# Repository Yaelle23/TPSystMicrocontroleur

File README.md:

# TPSystMicrocontroleur

# THOMAS Farima
# NOYON Yaëlle

# 1.2 Le Microcontrôleur sur Kicad
13- PB9 est relié à la masse pour inhiber l'état reset du uC.

14- Leur rôle est d'éviter la chute de tension

# 1.3 Le reste du schéma
3- C'est la première page qui indique les valeurs des condensateurs dans la datasheet

5- C'est la page 6 qui indique les condensateurs du DAC

6- La broche CS permet d'autoriser le fonctionnement

7- La broche LDAC permet d'avoir des sorties en simultanée

8- MISO n'est pas utilisé car le DAC n'envoie pas de data au uC

10- On le retrouve dans la datasheet de la sonde stlink v3

# 1.4 Affectation des empreintes
3- Ces valeurs font référence aux tailles des composants

4- LQFP, SOT-223, SOIC représentent les références des types de boitiers

#LQFP (Low Profile Quad Flat Pack ) :C'est un type de boîtier de circuit intégré destiné à être directement soudé sur circuit
imprimé.
#SOT-223 : C'est un boîtier monté en surface avec dissipateur thermique accru
#SOIC (Small Outline integrated Circuit) : Un circuit intégré à petit contour est un boîtier de circuit intégré monté en surface qui occupe une surface d'environ 30 à 50% inférieure à celle d'un boîtier double en ligne équivalent, avec une épaisseur typique inférieure de 70%.

# 3 Activation des LL drivers
2-Les fichiers générés sont liés au driver qu’on a positionné en LL :
    • main (.c et .h)
    • gpio (.c et .h)
    • adc (.c et .h)
    • spi (.c et .h)
    • stm32l0xx (.c et .h)
    • tim.c (.c et .h)
    • usart.c (.c et .h)
Ces codes nous permettent d’avoir accés à des registres différents

4-Selon la documentation de la HAL STM32L0 en plus des fonctions d’initialisation périphérique, les pilotes LL offrent un ensemble de fonctions « inline » pour un accès direct au registre. 

5-Dans le .h on définit la configuration des registres.

# 3.2 LED Simple
1-Configurer le timer de la LED pour obtenir une horloge de 16MHz et une résolution de 8bits. Ça veut dire que Counter period vaut 255.On déduis la valeur de PSC = 16000/256 = 63

# 3.2 LED avec timer
3-On veut obtenir un compteur à 1MHz ce qui signifie que la valeur de PSC doit être égal à 16. Le compteur doit reset toutes les millisecondes donc on paramètre ARR pour être égal à 1000.

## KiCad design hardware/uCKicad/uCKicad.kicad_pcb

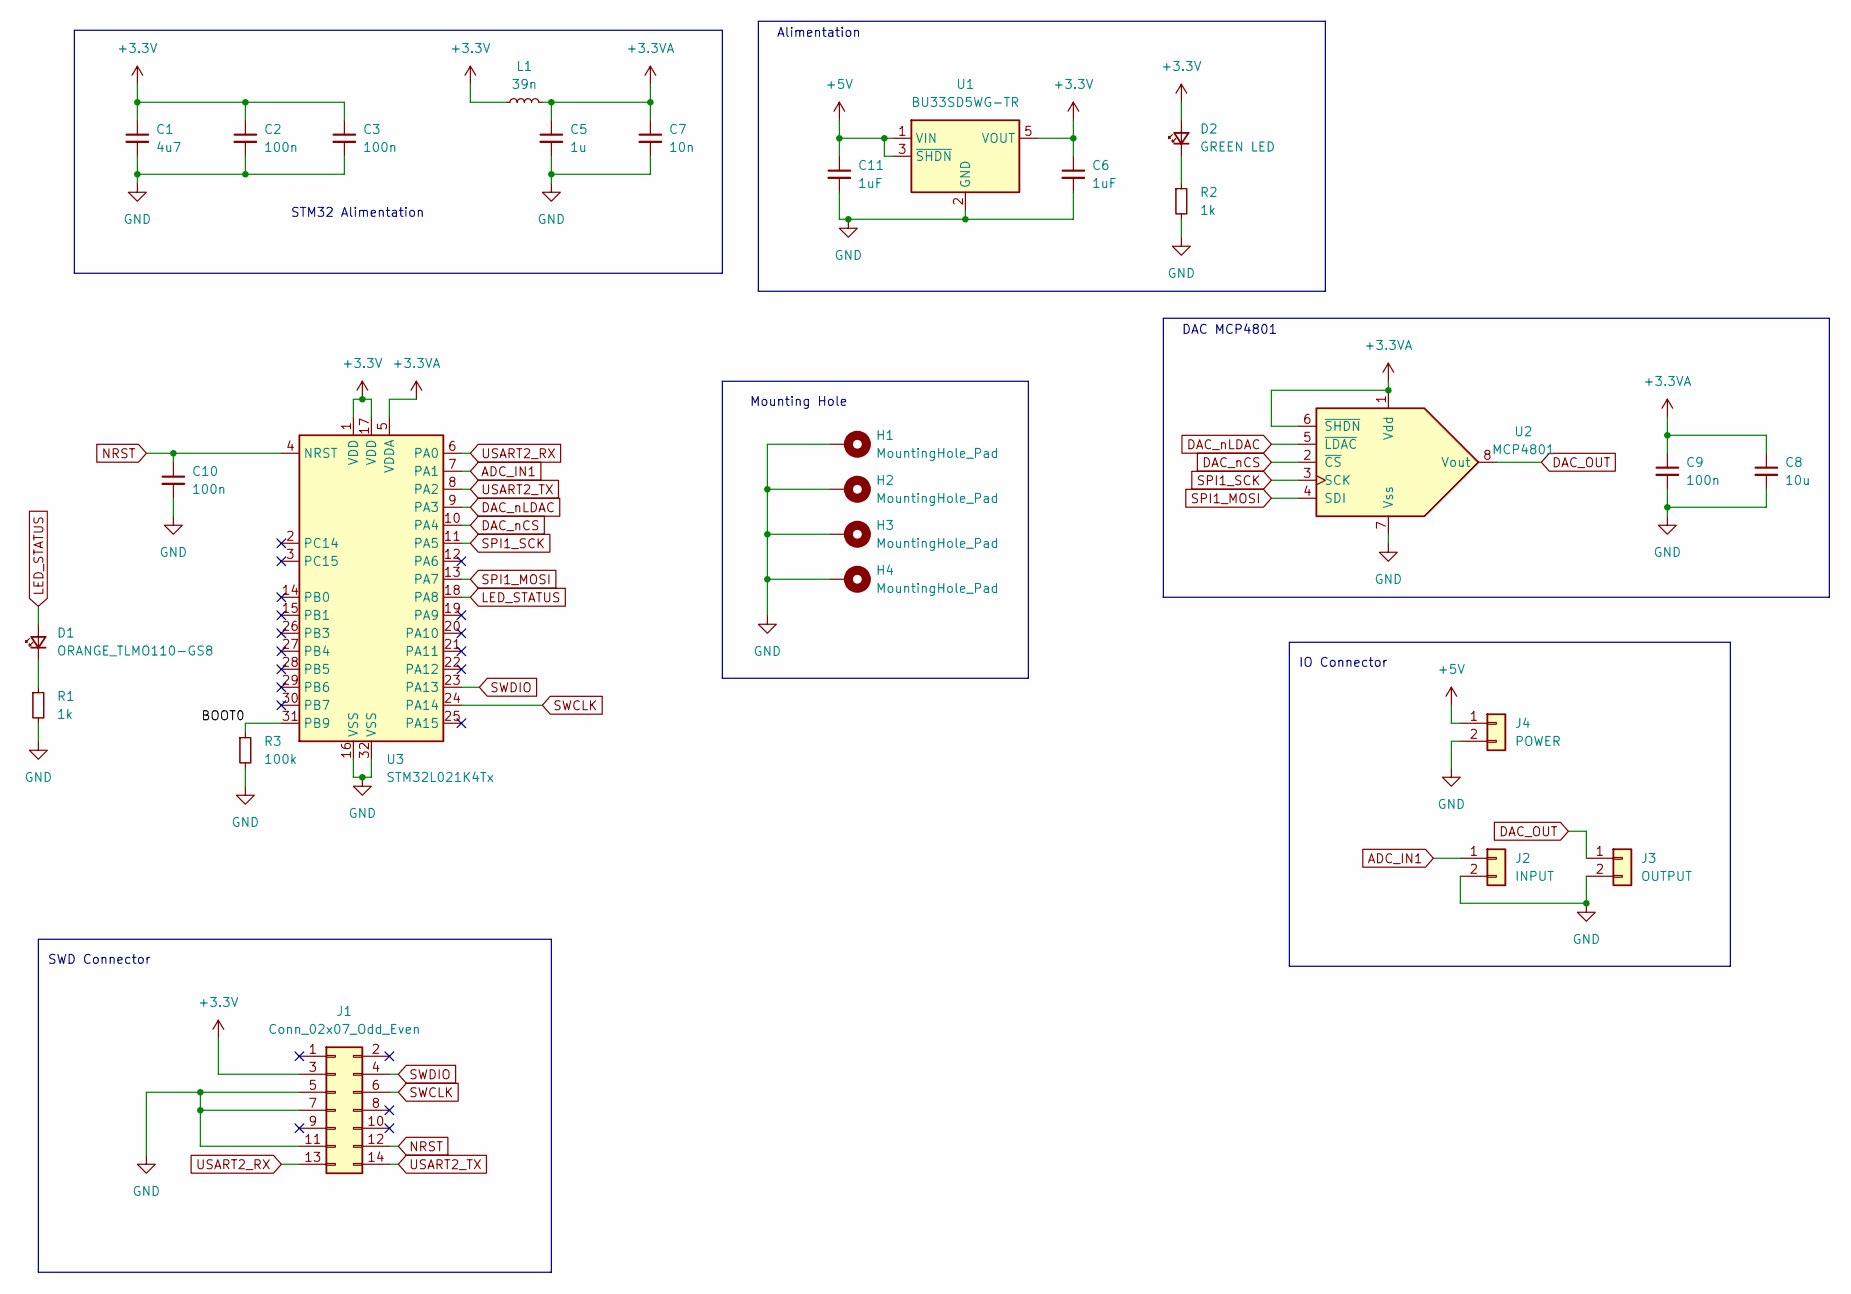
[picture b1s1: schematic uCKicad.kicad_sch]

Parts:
C1: 4u7; C_0805_2012Metric_Pad1.18x1.45mm_HandSolder
C2, C3, C9, C10: 100n; C_0805_2012Metric_Pad1.18x1.45mm_HandSolder
C5: 1u; C_0805_2012Metric_Pad1.18x1.45mm_HandSolder
C6, C11: 1uF; C_0805_2012Metric
C7: 10n; C_0805_2012Metric_Pad1.18x1.45mm_HandSolder
C8: 10u; C_0805_2012Metric
D1: ORANGE_TLMO110-GS8; LED_0603_1608Metric_Pad1.05x0.95mm_HandSolder
D2: GREEN LED; LED_0603_1608Metric_Pad1.05x0.95mm_HandSolder
H1, H2, H3, H4: MountingHole_Pad; MountingHole_3.2mm_M3_Pad
J1: Conn_02x07_Odd_Even; PinHeader_2x07_P1.27mm_Vertical_SMD
J2: INPUT; JST_XH_B2B-XH-A_1x02_P2.50mm_Vertical
J3: OUTPUT; JST_XH_B2B-XH-A_1x02_P2.50mm_Vertical
J4: POWER; JST_XH_B2B-XH-A_1x02_P2.50mm_Vertical
L1: 39n; L_0805_2012Metric_Pad1.05x1.20mm_HandSolder
R1, R2: 1k; R_0805_2012Metric_Pad1.20x1.40mm_HandSolder
R3: 100k; R_0805_2012Metric_Pad1.20x1.40mm_HandSolder
U1: BU33SD5WG-TR; SOT-23-5
U2: MCP4801; SOIC-8_3.9x4.9mm_P1.27mm
U3: STM32L021K4Tx; LQFP-32_7x7mm_P0.8mm

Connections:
+3.3V: C1.1, C2.1, C3.1, C6.1, D2.2 (A), J1.3, L1.1, U1.5 (VOUT), U3.1 (VDD), U3.17 (VDD)
+3.3VA: C5.1, C7.1, C8.1, C9.1, L1.2, U2.1 (Vdd), U2.6 (~SHDN), U3.5 (VDDA)
+5V: C11.1, J4.1, U1.1 (VIN), U1.3 (~SHDN)
/BOOT0: R3.1, U3.31 (PB9)
ADC_IN1: J2.1, U3.7 (PA1)
DAC_OUT: J3.1, U2.8 (Vout)
DAC_nCS: U2.2 (~CS), U3.10 (PA4)
DAC_nLDAC: U2.5 (~LDAC), U3.9 (PA3)
GND: C1.2, C2.2, C3.2, C5.2, C6.2, C7.2, C8.2, C9.2, C10.2, C11.2, H1.1, H2.1, H3.1, H4.1, J1.5, J1.7, J1.11, J2.2, J3.2, J4.2, R1.2, R2.2, R3.2, U1.2 (GND), U2.7 (Vss), U3.16 (VSS), U3.32 (VSS)
LED_STATUS: D1.2 (A), U3.18 (PA8)
NRST: C10.1, J1.12, U3.4 (NRST)
unnamed: D1.1 (K), R1.1
unnamed: D2.1 (K), R2.1
SPI1_MOSI: U2.4 (SDI), U3.13 (PA7)
SPI1_SCK: U2.3 (SCK), U3.11 (PA5)
SWCLK: J1.6, U3.24 (PA14)
SWDIO: J1.4, U3.23 (PA13)
USART2_RX: J1.13, U3.6 (PA0)
USART2_TX: J1.14, U3.8 (PA2)

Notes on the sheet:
IO Connector
DAC MCP4801
Mounting Hole
Alimentation
SWD Connector
STM32 Alimentation

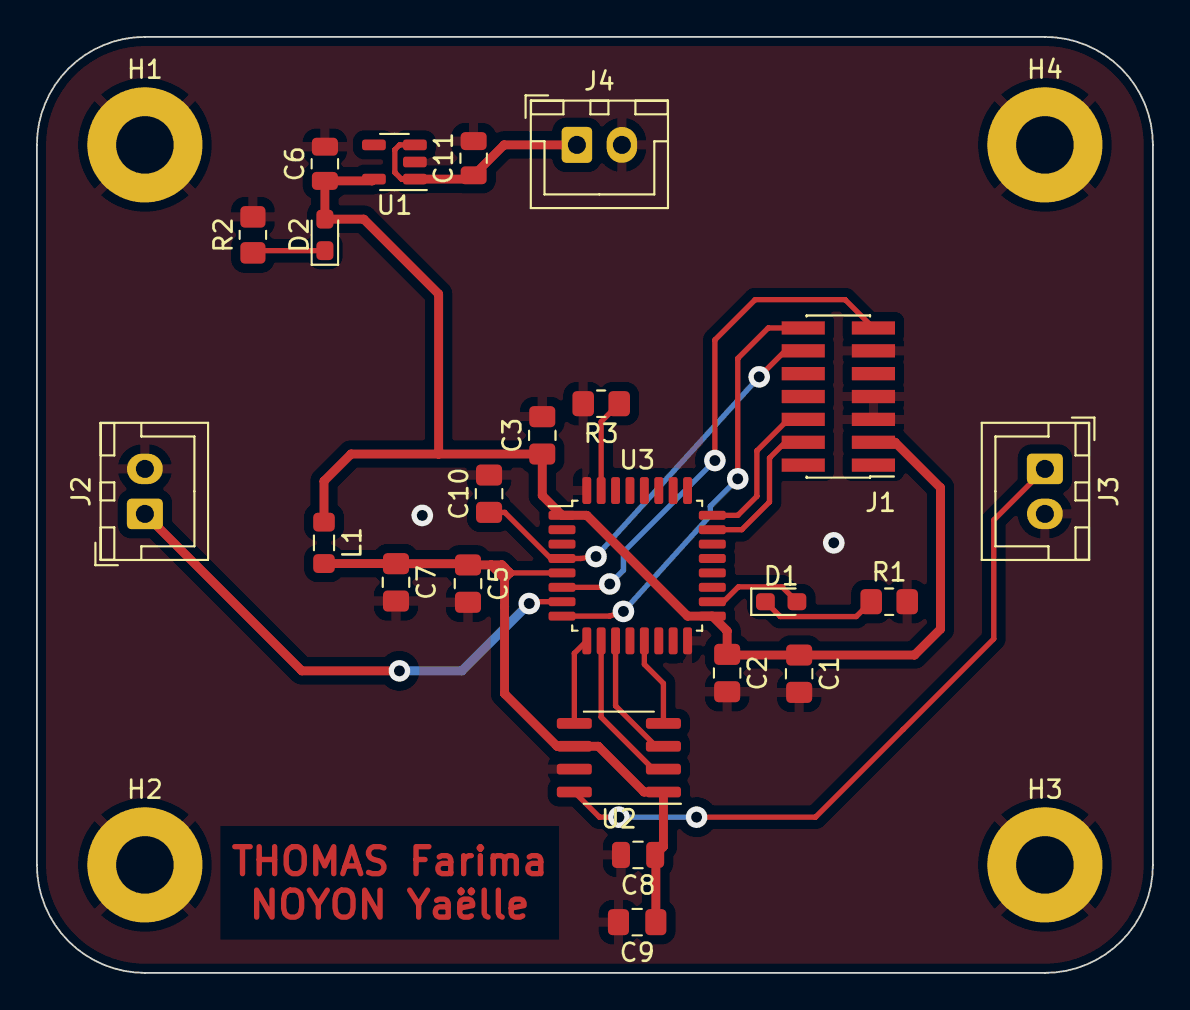
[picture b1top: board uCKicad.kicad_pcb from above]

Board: 2 copper layers, 62.0 x 52.0 mm, 27 parts (0 on the bottom side), 19 nets.

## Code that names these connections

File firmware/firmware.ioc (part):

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Mcu.Name=STM32L021K4Tx
Mcu.Package=LQFP32
Mcu.UserName=STM32L021K4Tx
PA0-CK_IN.Mode=Asynchronous
PA0-CK_IN.Signal=USART2_RX
PA1.Mode=IN1
PA1.Signal=ADC_IN1
PA13.Mode=Serial_Wire
PA13.Signal=SYS_SWDIO
PA14.Mode=Serial_Wire
PA14.Signal=SYS_SWCLK
PA2.Mode=Asynchronous
PA2.Signal=USART2_TX
PA3.GPIOParameters=GPIO_Label
PA3.GPIO_Label=DAC_nLDAC
PA3.Signal=GPIO_Output
PA4.GPIOParameters=GPIO_Label
PA4.GPIO_Label=DAC_nCS
PA4.Signal=GPIO_Output
PA5.Mode=Full_Duplex_Master
PA5.Signal=SPI1_SCK
PA6.Mode=Full_Duplex_Master
PA6.Signal=SPI1_MISO
PA7.Mode=Full_Duplex_Master
PA7.Signal=SPI1_MOSI
PA8.Signal=S_TIM2_CH1
RCC.HSE_VALUE=8000000
RCC.SYSCLKFreq_VALUE=32000000
RCC.SYSCLKSource=RCC_SYSCLKSOURCE_PLLCLK
board=custom

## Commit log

2023-02-15 Dossier Datasheet
2023-02-15 Création de la structure du projet
2023-02-15 Le microcontroleur sous KiCAD
2023-02-15 Le microcontroleur sous KiCAD part 2
2023-02-15 Le reste du schema
2023-02-16 on essaie de sauver le PC
2023-02-16 Placement des composants
2023-02-16 Routage
2023-02-16 Modification du README
2023-02-16 Generation des fichiers de fabrication
2023-03-10 Last commit
